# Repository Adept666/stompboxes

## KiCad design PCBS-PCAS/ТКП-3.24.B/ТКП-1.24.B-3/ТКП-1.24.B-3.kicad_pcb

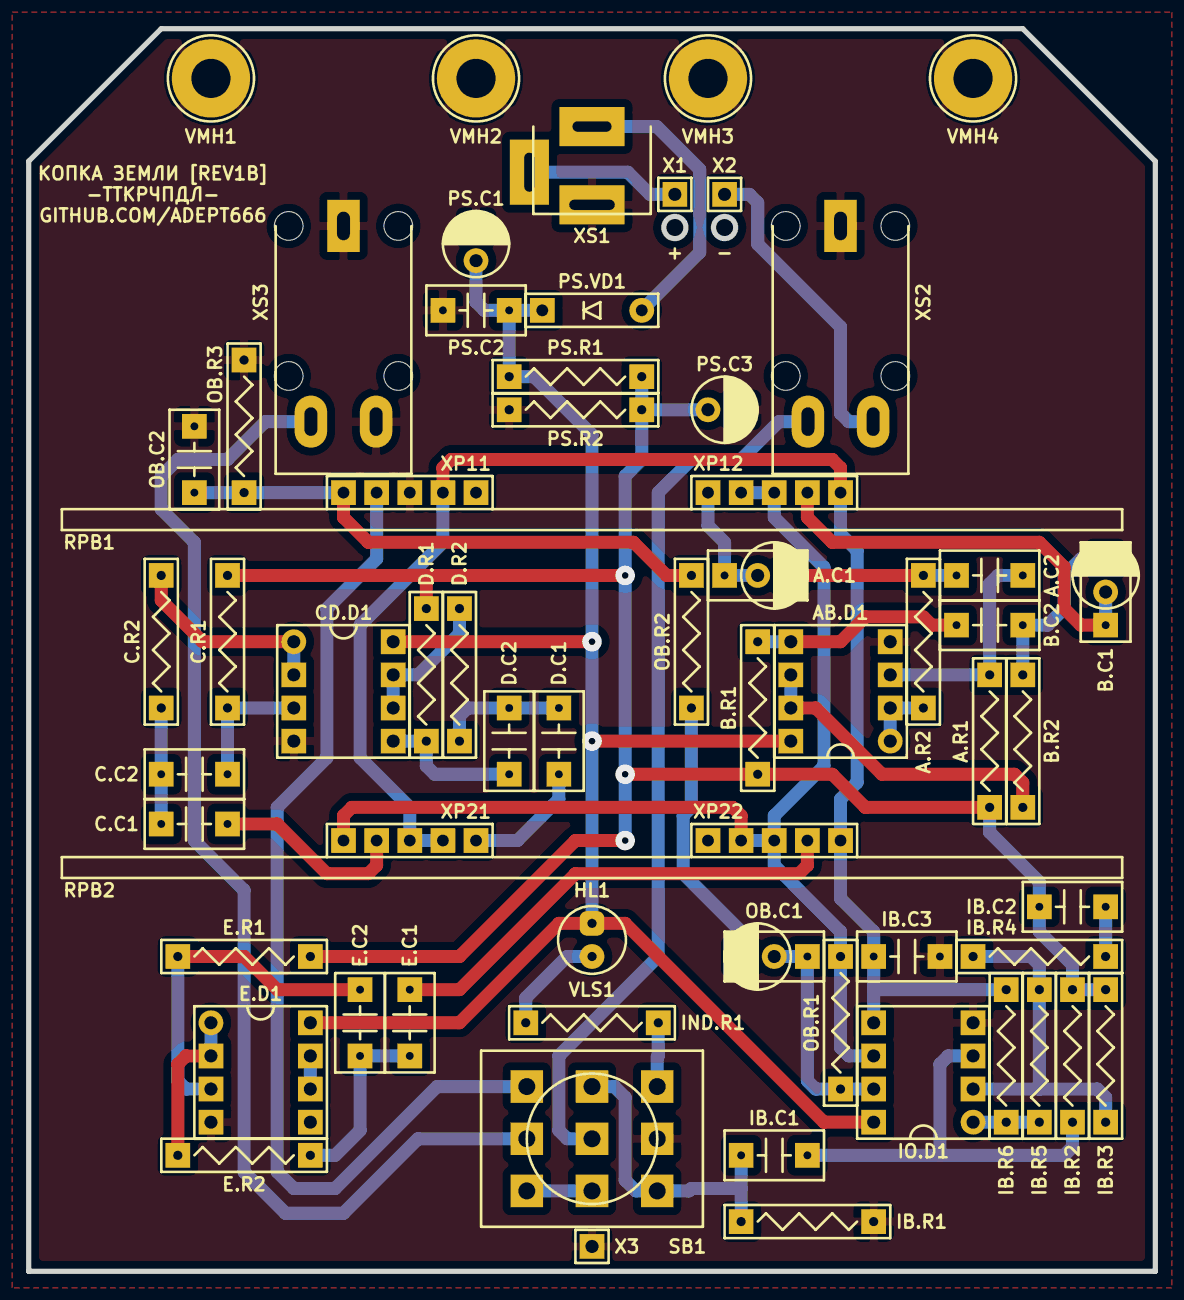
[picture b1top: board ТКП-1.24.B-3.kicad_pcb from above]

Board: 2 copper layers, 86.4 x 95.3 mm, 63 parts (0 on the bottom side), 43 nets.

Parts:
A.C1: 225; C-DISK-D04.2-T03.0-P05.08-d0.5-OR-CP-RADIAL-D05.0-P02.0-CLS
A.C2: 473; C-DISK-D04.2-T03.0-P05.08-d0.5
A.R1: 124; R-MFR-25
A.R2: 471; R-MFR-25
AB.D1: 4558; P-DIP-08
B.C1: 105; C-DISK-D04.2-T03.0-P05.08-d0.5-OR-CP-RADIAL-D05.0-P02.0-CLS
B.C2: 333; C-DISK-D04.2-T03.0-P05.08-d0.5
B.R1: 104; R-MFR-25
B.R2: 471; R-MFR-25
C.C1: 154; C-DISK-D04.2-T03.0-P05.08-d0.5
C.C2: 682; C-DISK-D04.2-T03.0-P05.08-d0.5
C.R1: 104; R-MFR-25
C.R2: 102; R-MFR-25
CD.D1: 4558; P-DIP-08
D.C1: 683; C-DISK-D04.2-T03.0-P05.08-d0.5
D.C2: 332; C-DISK-D04.2-T03.0-P05.08-d0.5
D.R1: 104; R-MFR-25
D.R2: 102; R-MFR-25
E.C1: 223; C-DISK-D04.2-T03.0-P05.08-d0.5
E.C2: 681; C-DISK-D04.2-T03.0-P05.08-d0.5
E.D1: 4558; P-DIP-08
E.R1: 104; R-MFR-25
E.R2: 102; R-MFR-25
GB1: X; B-PP3-HV
HL1: FYL-5013UWC; LED-ROUND-05.0-UNI-SH-SPACER-PNL-5.3
IB.C1, IB.C2: 103; C-DISK-D04.2-T03.0-P05.08-d0.5
IB.C3: 151; C-DISK-D04.2-T03.0-P05.08-d0.5
IB.R1: 225; R-MFR-25
IB.R2: 474; R-MFR-25
IB.R3, IB.R5, IB.R6: 103; R-MFR-25
IB.R4: 102; R-MFR-25
IND.R1: 103; R-MFR-25
IO.D1: 4558; P-DIP-08
OB.C1: 105; C-DISK-D04.2-T03.0-P05.08-d0.5-OR-CP-RADIAL-D05.0-P02.0-CLS
OB.C2: 103; C-DISK-D04.2-T03.0-P05.08-d0.5
OB.R1, OB.R2, OB.R3: 103; R-MFR-25
PS.C1: 107; CP-RADIAL-D05.0-P02.0-CLS
PS.C2: 104; C-DISK-D04.2-T03.0-P05.08-d0.5
PS.C3: 476; CP-RADIAL-D05.0-P02.0-CLS
PS.R1, PS.R2: 473; R-MFR-25
PS.VD1: 5817; P-DO-41
RPB1, RPB2: B50K-B50K-B50K; RPB-1590BB-18-3x17-1.6-PNL-7.2
SB1: PBS-24-302SP; SW-PBS-24-302SP-2.5-PNL-12.0
VE1: ТКП-6.1.1.A1.A1.A.1-1; ТКП-6.1.1.A1.A1.A
VE2: ТКП-6.1.3.A2.C1.2-1.B2.C1; ТКП-6.1.3.A2
VLS1: BR-17.8; VLS-BR
VMH1, VMH2, VMH3, VMH4: DI5M3x20; VMH-STA-DA5-PNL-3.0
X1, X2, X3: X; CON-PAD-S-1.0-1.9
XS1: DC-005; CON-DC-005
XS2, XS3: PJ-309; CON-ST-008X-04

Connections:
/BOOST-RAIL: IO.D1.6, OB.R1.1, RPB1.23, RPB1.33, RPB2.13, RPB2.23, RPB2.33
/CUT-RAIL: IB.C3.1, IB.R6.2, IO.D1.5, RPB1.21, RPB1.31, RPB2.11, RPB2.21, RPB2.31
/IN-CIR: IB.C1.1, IB.R1.2, SB1.NC3, SB1.NO2
/IN-CON: SB1.COM2, XS2.T
/LED: IND.R1.1, SB1.NO3
/OUT-CIR: RPB1.12, SB1.NO1
/OUT-CON: SB1.COM1, XS3.T
/PP3-NEG: X2.1, XS2.R
/PP3-POS: X1.1, XS1.SN
COM: AB.D1.4, CD.D1.4, E.D1.4, IB.C3.2, IB.R1.1, IO.D1.4, OB.C2.2, OB.R3.1, PS.C1.-, PS.C2.2, PS.C3.-, PS.R2.1, RPB1.11, SB1.COM3, VMH1.0, VMH2.0, VMH3.0, VMH4.0, X3.1, XS1.C, XS2.S, XS3.R, XS3.S
unnamed: A.C1.+, RPB1.22
unnamed: A.C1.-, A.C2.1, A.R2.1
unnamed: A.C2.2, A.R1.2, AB.D1.3
unnamed: A.R2.2, AB.D1.1, AB.D1.2
unnamed: AB.D1.5, B.C2.2, B.R1.2
unnamed: AB.D1.6, AB.D1.7, B.R2.2
unnamed: B.C1.+, RPB1.32
unnamed: B.C1.-, B.C2.1, B.R2.1
unnamed: C.C1.1, RPB2.12
unnamed: C.C1.2, C.C2.1, C.R2.1
unnamed: C.C2.2, C.R1.2, CD.D1.3
unnamed: C.R2.2, CD.D1.1, CD.D1.2
unnamed: CD.D1.5, D.C2.2, D.R1.2
unnamed: CD.D1.6, CD.D1.7, D.R2.2
unnamed: D.C1.1, RPB2.22
unnamed: D.C1.2, D.C2.1, D.R2.1
unnamed: E.C1.1, RPB2.32
unnamed: E.C1.2, E.C2.1, E.R2.1
unnamed: E.C2.2, E.D1.3, E.R1.2
unnamed: E.D1.1, E.D1.2, E.R2.2
unnamed: E.D1.6, E.D1.7
unnamed: HL1.C, IND.R1.2
unnamed: IB.C1.2, IB.R2.2, IO.D1.3
unnamed: IB.C2.2, IB.R4.1
unnamed: IB.R3.2, IB.R4.2, IB.R5.1, IO.D1.2
unnamed: IB.R5.2, IB.R6.1, IO.D1.1
unnamed: IO.D1.7, OB.C1.+, OB.R1.2
unnamed: OB.C1.-, OB.R2.1
unnamed: OB.C2.1, OB.R2.2, OB.R3.2, RPB1.13
unnamed: PS.VD1.A, XS1.S
unnamed: SB1.NC1, SB1.NC2
V: AB.D1.8, CD.D1.8, E.D1.8, HL1.A, IO.D1.8, PS.C1.+, PS.C2.1, PS.R1.2, PS.VD1.C
VREF: A.R1.1, B.R1.1, C.R1.1, D.R1.1, E.R1.1, IB.C2.1, IB.R2.1, IB.R3.1, PS.C3.+, PS.R1.1, PS.R2.2

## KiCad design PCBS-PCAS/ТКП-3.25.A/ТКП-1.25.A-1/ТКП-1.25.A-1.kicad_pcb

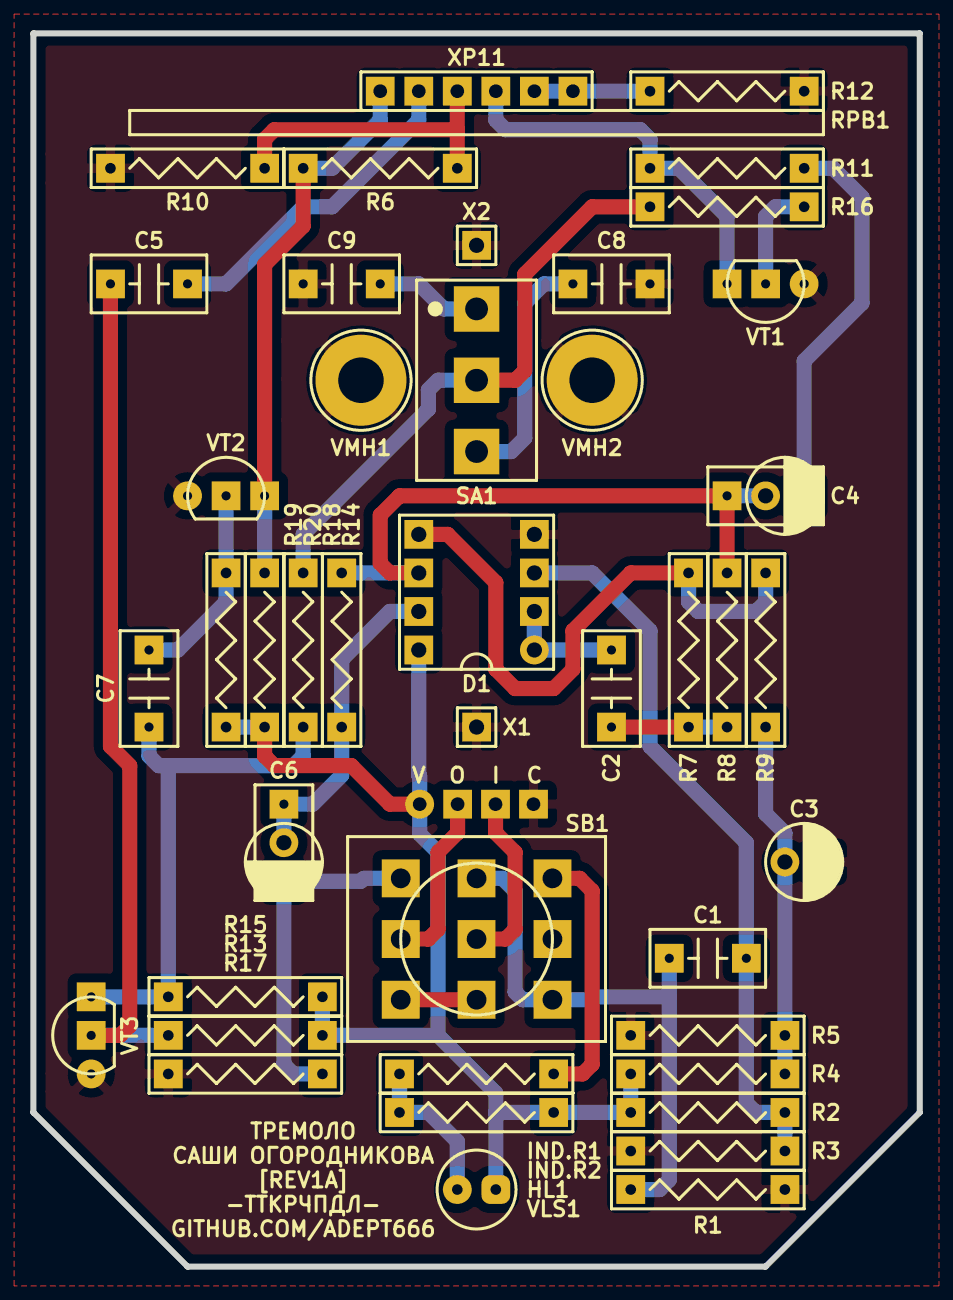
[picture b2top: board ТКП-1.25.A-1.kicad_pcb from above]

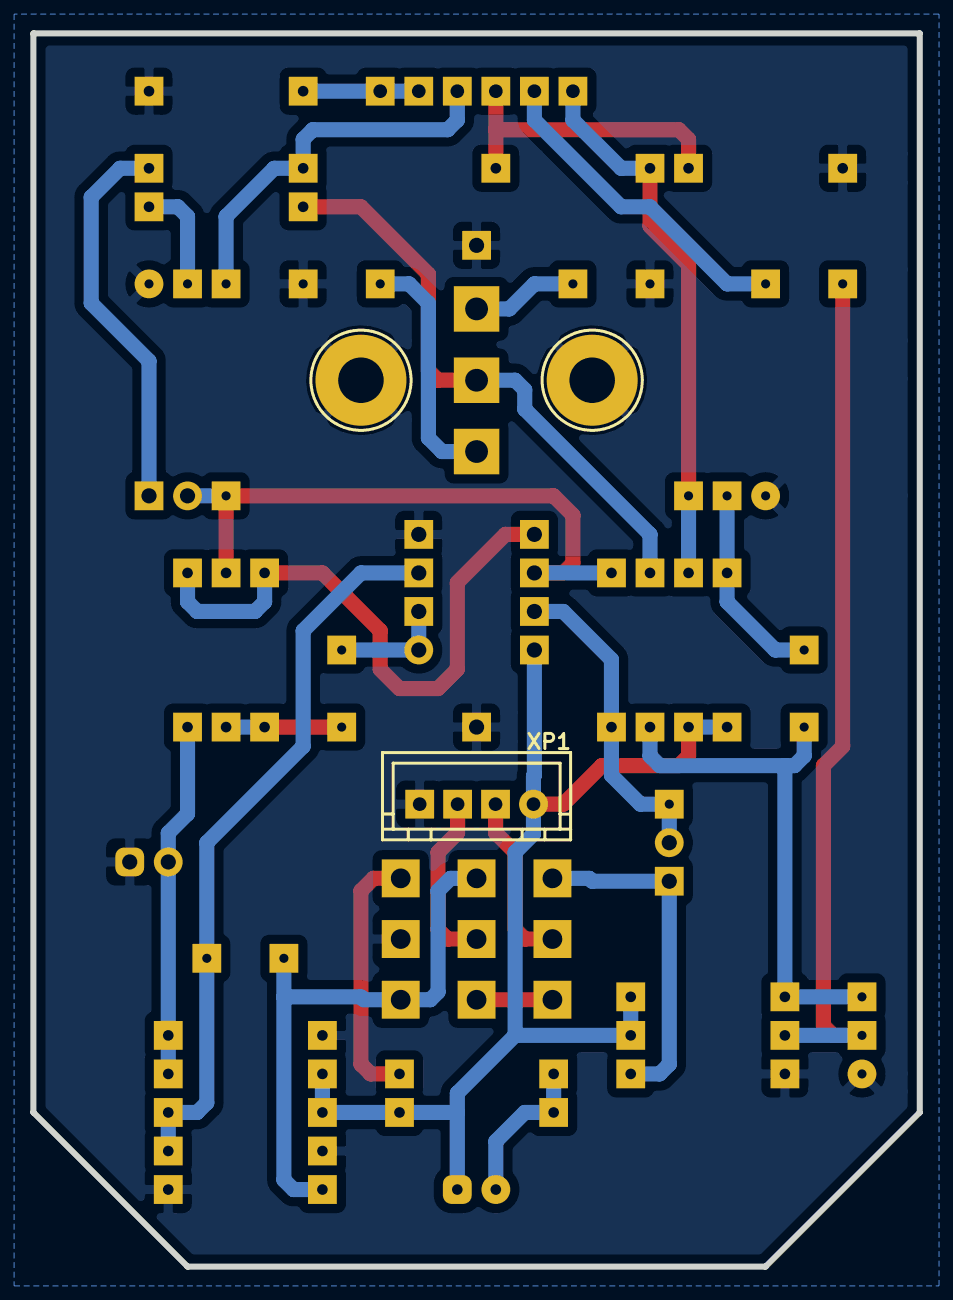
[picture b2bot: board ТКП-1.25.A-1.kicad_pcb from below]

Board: 2 copper layers, 58.4 x 81.3 mm, 61 parts (14 on the bottom side), 29 nets.

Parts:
C1, C2: 104; C-DISK-D04.2-T03.0-P05.08-d0.5
C3: 226; CP-RADIAL-D05.0-P02.0-CLS
C4: 475; C-DISK-D04.2-T03.0-P05.08-d0.5-OR-CP-RADIAL-D05.0-P02.0-CLS
C5, C7: 474; C-DISK-D04.2-T03.0-P05.08-d0.5
C6: 105; C-DISK-D04.2-T03.0-P05.08-d0.5-OR-CP-RADIAL-D05.0-P02.0-CLS
C8: 224; C-DISK-D04.2-T03.0-P05.08-d0.5
C9: 223; C-DISK-D04.2-T03.0-P05.08-d0.5
D1: 4558; P-DIP-08
HL1: FYL-5013URC; LED-ROUND-05.0-UNI-SH-SPACER-PNL-5.3
IND.R1: 472; R-MFR-25
IND.R2: X; R-MFR-25
R1, R13: 225; R-MFR-25
R2, R3: 105; R-MFR-25
R4: 273; R-MFR-25
R5, R8: 303; R-MFR-25
R6: 683; R-MFR-25
R7, R15, R17, R20: 473; R-MFR-25
R9: 393; R-MFR-25
R10: 112; R-MFR-25
R11, R12: 103; R-MFR-25
R14: 333; R-MFR-25
R16, R18: 204; R-MFR-25
R19: 334; R-MFR-25
RPB1: A100K-A100K; RPB-1590N1-18-2x17-1.6-PNL-7.4-2.8
SA1: MTS-102-A2; SW-MTS-102-A2-3.0-PNL-6.0
SB1: PBS-24-302SP; SW-PBS-24-302SP-2.5-PNL-13.0
VE1: 1590N1; 1590N1_A1
VJ1.1, VJ1.2, VJ2.1, VJ2.2, VJ3.1, VJ3.2, VJ4.1, VJ4.2, VJ4.3: BOTTOM; VJ
VLS1: BR-12.7; VLS-BR
VMH1, VMH2: DI5M3x18; VMH-STA-DA5-PNL-3.0
VT1, VT2, VT3: 5088; P-TO-92-E-B-C
VTC1, VTC3, VTC4, VTC5: BOTTOM; VTC
VTC2: TOP; VTC
X1, X2: COM; CON-PAD-S-1.0-1.9
XB1: 1590N1 Connector Board; XB-1590N1
XP1: B4B-XH-A; CON-XH-B4B-A

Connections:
/IN-CIR: C1.1, R1.2, SB1.NC3, SB1.NO2
/IN-CON: SB1.COM2, XP1.3
/LED: IND.R1.1, SB1.NO3
/OUT-CIR: C6.-, R17.2, SB1.NO1
/OUT-CON: SB1.COM1, XP1.2
COM: C3.-, C8.2, C9.2, D1.4, R1.1, R3.1, R5.1, R10.1, R12.1, R17.1, SB1.COM3, VMH1.0, VMH2.0, VT1.E, VT2.E, VT3.E, X1.1, X2.1, XP1.4
unnamed: C1.2, D1.3, R2.1, R3.2
unnamed: C2.1, D1.1, D1.2
unnamed: C2.2, R7.1, R8.1
unnamed: C3.+, R4.1, R5.2, R9.1
unnamed: C4.+, D1.6, R8.2, R14.1
unnamed: C4.-, R11.2
unnamed: C5.1, RPB1.12
unnamed: C5.2, R13.1, VT3.B
unnamed: C6.+, D1.7, R14.2
unnamed: C7.1, R15.1, R18.1, VT3.C
unnamed: C7.2, R19.1, VT2.B
unnamed: C8.1, SA1.NO
unnamed: C9.1, SA1.NC
unnamed: D1.5, R7.2, R9.2
unnamed: HL1.C, IND.R1.2, IND.R2.1
unnamed: R6.1, R10.2, RPB1.11, VJ1.2.1, VJ2.1.1, VTC2.1
unnamed: R11.1, RPB1.23, VJ3.1.1, VJ4.1.1, VT1.C, VTC3.1
unnamed: R12.2, RPB1.21, RPB1.22, VJ3.2.1, VJ4.2.1, VJ4.3.1, VTC4.1, VTC5.1
unnamed: R16.1, VT1.B
unnamed: R16.2, R18.2, SA1.COM
unnamed: R6.2, R20.1, RPB1.13, VJ1.1.1, VJ2.2.1, VT2.C, VTC1.1
unnamed: SB1.NC1, SB1.NC2
V: D1.8, HL1.A, IND.R2.2, R2.2, R4.2, R13.2, R15.2, R19.2, R20.2, XP1.1

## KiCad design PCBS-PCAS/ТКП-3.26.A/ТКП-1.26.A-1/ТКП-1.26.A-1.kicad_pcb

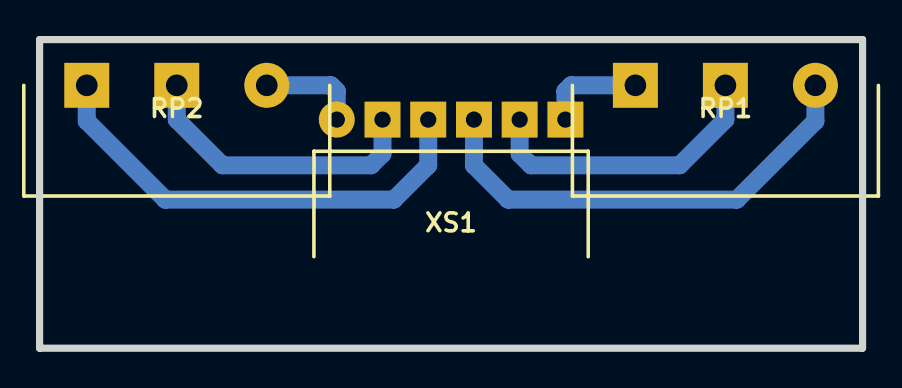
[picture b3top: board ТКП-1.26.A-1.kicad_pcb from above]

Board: 2 copper layers, 45.7 x 17.1 mm, 3 parts (0 on the bottom side), 6 nets.

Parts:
RP1: RP1: A100K; RP-PDB181-K-20-P
RP2: RP2: A100K; RP-PDB181-K-20-P
XS1: PBS-06R; CON-PBS-06R

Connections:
unnamed: RP1.1, XS1.4
unnamed: RP1.2, XS1.5
unnamed: RP1.3, XS1.6
unnamed: RP2.1, XS1.1
unnamed: RP2.2, XS1.2
unnamed: RP2.3, XS1.3

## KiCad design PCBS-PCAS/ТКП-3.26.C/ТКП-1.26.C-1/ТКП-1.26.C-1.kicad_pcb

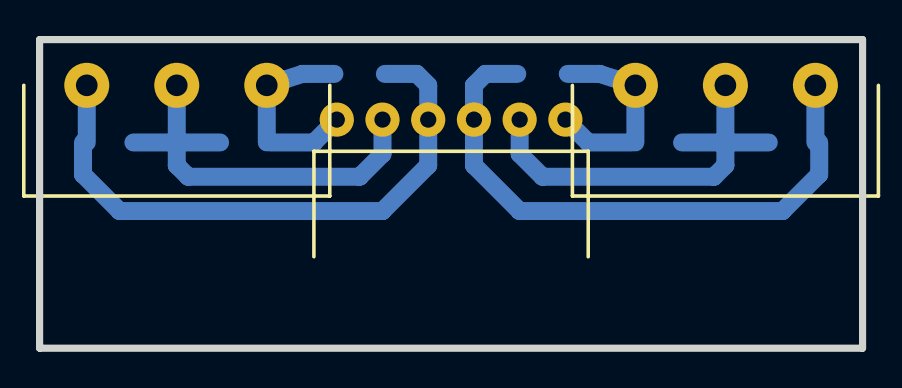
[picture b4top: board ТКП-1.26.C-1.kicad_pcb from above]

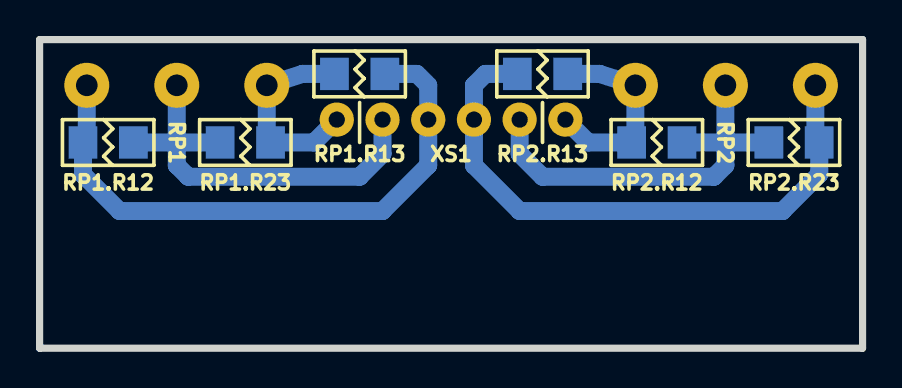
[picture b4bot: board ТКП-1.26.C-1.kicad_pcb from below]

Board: 2 copper layers, 45.7 x 17.1 mm, 9 parts (6 on the bottom side), 6 nets.

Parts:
RP1, RP2: A100K; RP-PDB181-K-20-P-CIRCULAR
RP1.R12, RP1.R13, RP1.R23, RP2.R12, RP2.R13, RP2.R23: X; R-SM-1206
XS1: PBS-06R; CON-PBS-06R-CIRCULAR

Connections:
unnamed: RP1.1, RP1.R12.2, RP1.R13.2, XS1.4
unnamed: RP1.2, RP1.R12.1, RP1.R23.2, XS1.5
unnamed: RP1.3, RP1.R13.1, RP1.R23.1, XS1.6
unnamed: RP2.1, RP2.R12.2, RP2.R13.2, XS1.1
unnamed: RP2.2, RP2.R12.1, RP2.R23.2, XS1.2
unnamed: RP2.3, RP2.R13.1, RP2.R23.1, XS1.3

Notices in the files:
PCBS-PCAS/ТКП-3.24.B/ТКП-1.24.B-3/ТКП-1.24.B-3.kicad_pcb:
This project is licensed under GNU General Public License v3.0 or later
